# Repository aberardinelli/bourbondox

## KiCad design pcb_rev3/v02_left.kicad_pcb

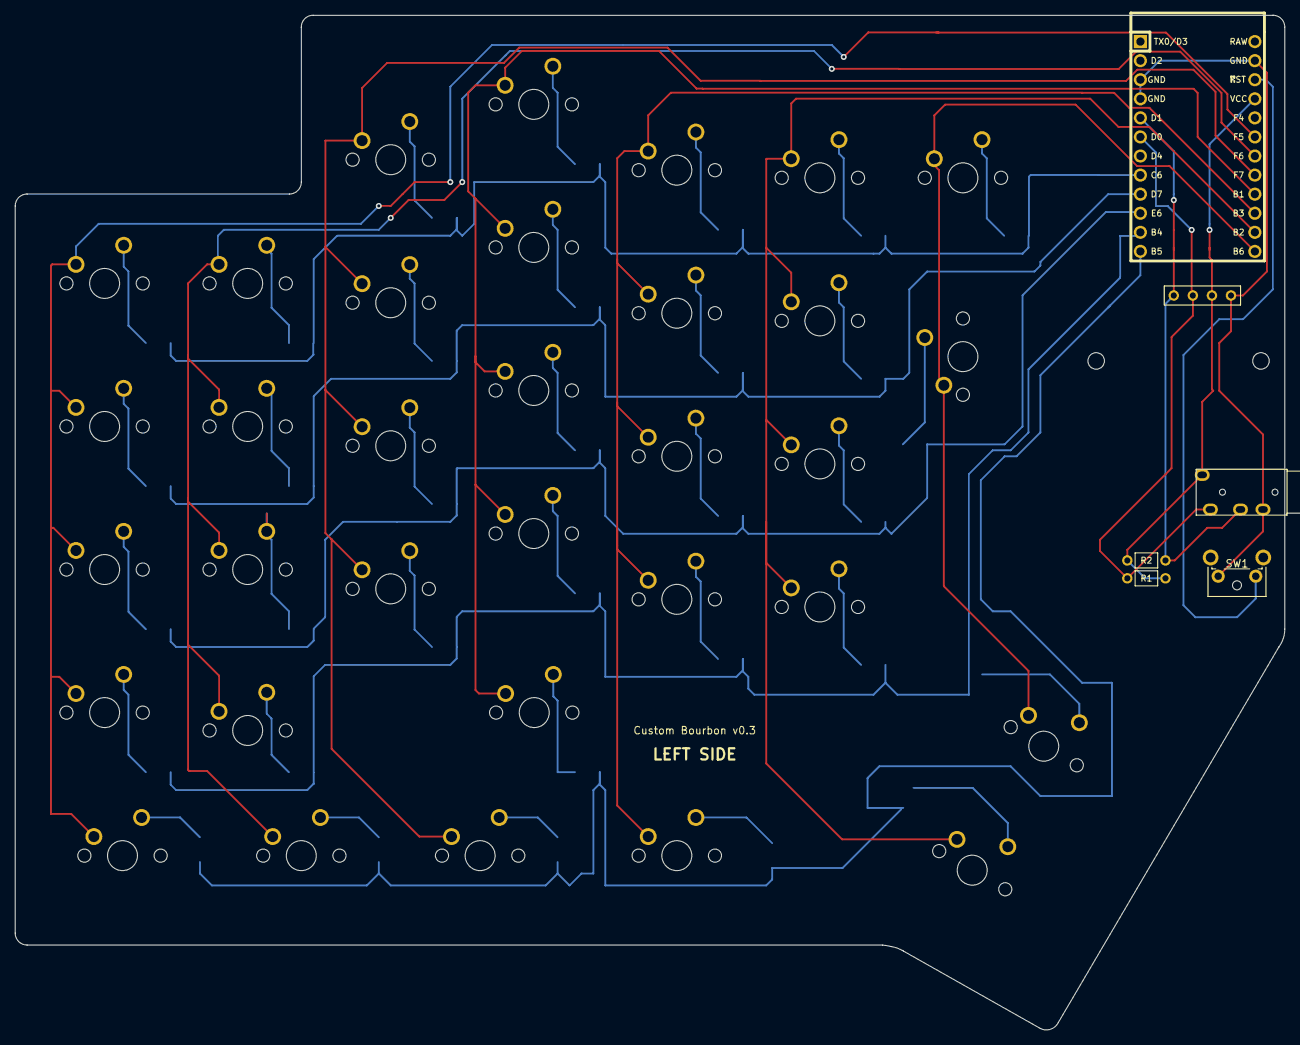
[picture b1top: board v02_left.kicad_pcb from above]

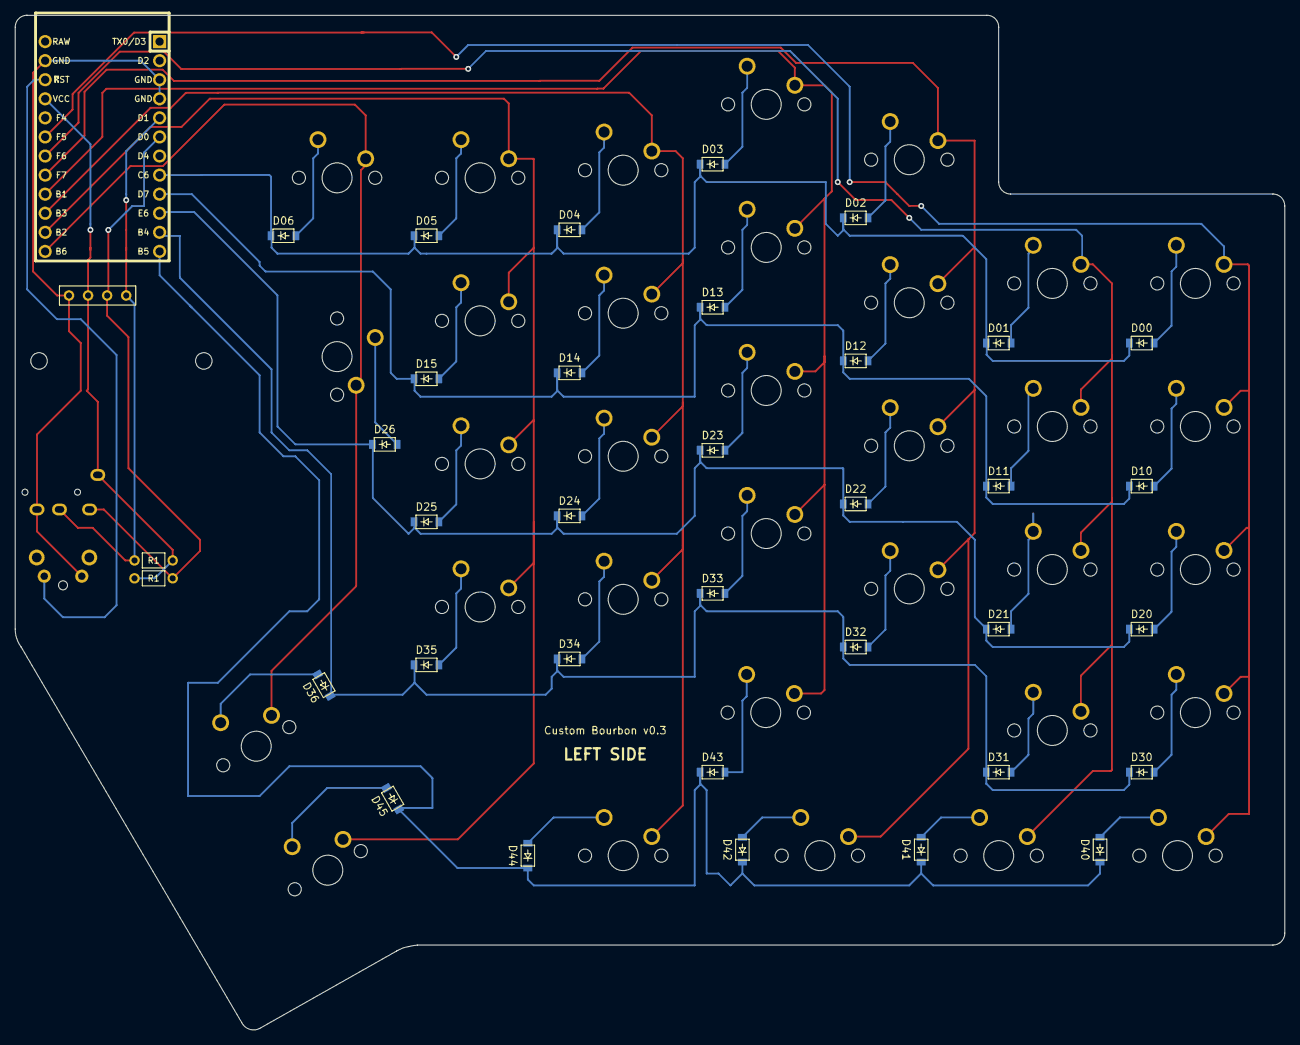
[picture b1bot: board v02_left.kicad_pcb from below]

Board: 2 copper layers, 169.1 x 135.1 mm, 74 parts (33 on the bottom side), 50 nets.

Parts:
D00, D01, D02, D03, D04, D05, D06, D10, D11, D12, D13, D14, D15, D20, D21, D22, D23, D24, D25, D26, D30, D31, D32, D33, D34, D35, D36, D40, D41, D42, D43, D44, D45: D_Small; D_SOD-123
H1, H2: Hole; HOLE_M2
J1: Audio-Jack-4; TRRS-PJ-320A
MX00, MX01, MX02, MX03, MX04, MX05, MX06, MX10, MX11, MX12, MX13, MX14, MX15, MX20, MX21, MX22, MX23, MX24, MX25, MX30, MX31, MX32, MX33, MX34, MX35, MX43: MX-NoLED; MXOnly-1U-NoLED
MX26, MX36, MX44, MX45: MX-NoLED; MXOnly-1.5U-NoLED
MX40, MX41, MX42: MX-NoLED; MXOnly-1.25U-NoLED
OL1: OLED; OLED_4Pin
R1, R2: 4.7k; RESISTOR_mini
SW1: SW_Push; SW_Tactile_SPST_Angled_MJTP1117
U1: ProMicro; ArduinoProMicro

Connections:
GND: J1.4, OL1.4, SW1.2, U1.3, U1.4, U1.23
unnamed: D00.2, MX00.2
unnamed: D01.2, MX01.2
unnamed: D02.2, MX02.2
unnamed: D03.2, MX03.2
unnamed: D04.2, MX04.2
unnamed: D05.2, MX05.2
unnamed: D06.2, MX06.2
unnamed: D10.2, MX10.2
unnamed: D11.2, MX11.2
unnamed: D12.2, MX12.2
unnamed: D13.2, MX13.2
unnamed: D14.2, MX14.2
unnamed: D15.2, MX15.2
unnamed: D20.2, MX20.2
unnamed: D21.2, MX21.2
unnamed: D22.2, MX22.2
unnamed: D23.2, MX23.2
unnamed: D24.2, MX24.2
unnamed: D25.2, MX25.2
unnamed: D26.2, MX26.2
unnamed: D30.2, MX30.2
unnamed: D31.2, MX31.2
unnamed: D32.2, MX32.2
unnamed: D33.2, MX33.2
unnamed: D34.2, MX34.2
unnamed: D35.2, MX35.2
unnamed: D36.2, MX36.2
unnamed: D40.2, MX40.2
unnamed: D41.2, MX41.2
unnamed: D42.2, MX42.2
unnamed: D43.2, MX43.2
unnamed: D44.2, MX44.2
unnamed: D45.2, MX45.2
RESET: SW1.1, U1.22
SCL: J1.2, OL1.2, R1.1, U1.6
SDA: J1.3, OL1.1, R2.1, U1.5
VCC: J1.1, OL1.3, R1.2, R2.2, U1.21
col0: MX00.1, MX10.1, MX20.1, MX30.1, MX40.1, U1.19
col1: MX01.1, MX11.1, MX21.1, MX31.1, MX41.1, U1.18
col2: MX02.1, MX12.1, MX22.1, MX32.1, MX42.1, U1.17
col3: MX03.1, MX13.1, MX23.1, MX33.1, MX43.1, U1.16
col4: MX04.1, MX14.1, MX24.1, MX34.1, MX44.1, U1.15
col5: MX05.1, MX15.1, MX25.1, MX35.1, MX45.1, U1.14
col6: MX06.1, MX26.1, MX36.1, U1.13
row0: D00.1, D01.1, D02.1, D03.1, D04.1, D05.1, D06.1, U1.8
row1: D10.1, D11.1, D12.1, D13.1, D14.1, D15.1, U1.9
row2: D20.1, D21.1, D22.1, D23.1, D24.1, D25.1, D26.1, U1.10
row3: D30.1, D31.1, D32.1, D33.1, D34.1, D35.1, D36.1, U1.11
row4: D40.1, D41.1, D42.1, D43.1, D44.1, D45.1, U1.12
